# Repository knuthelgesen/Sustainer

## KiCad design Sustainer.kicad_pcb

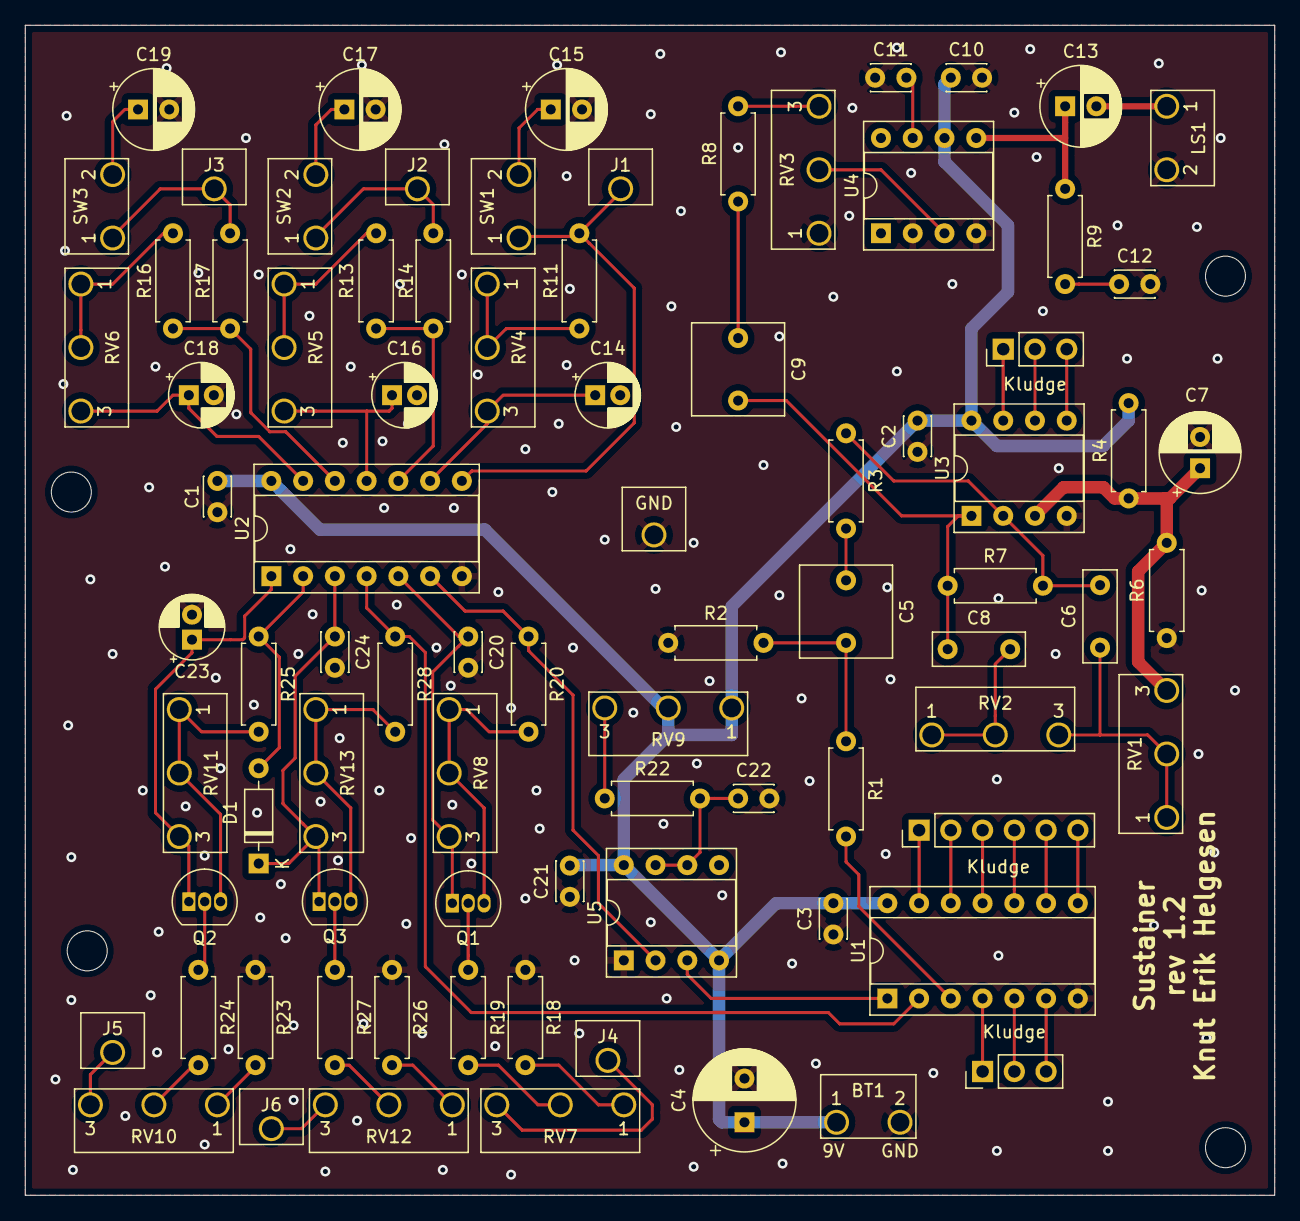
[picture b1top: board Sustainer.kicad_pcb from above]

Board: 2 copper layers, 99.9 x 93.6 mm, 81 parts (0 on the bottom side), 55 nets.

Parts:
BT1: 9V; Connector_2x1_1.5mm
C1, C2, C3, C10, C11, C20, C21, C22, C24: 0.1u; C_Disc_D3.0mm_W2.0mm_P2.50mm
C4: 470u; CP_Radial_D8.0mm_P3.50mm
C5, C9: 1u; C_Rect_L7.2mm_W7.2mm_P5.00mm_FKS2_FKP2_MKS2_MKP2
C6, C8: 0.001u; C_Rect_L7.2mm_W2.5mm_P5.00mm_FKS2_FKP2_MKS2_MKP2
C7, C13, C15, C17, C19: 220u; CP_Radial_D6.3mm_P2.50mm
C12: 0.047u; C_Disc_D3.0mm_W2.0mm_P2.50mm
C14, C23: 1u; CP_Radial_D5.0mm_P2.00mm
C16: 10u; CP_Radial_D5.0mm_P2.00mm
C18: 22u; CP_Radial_D5.0mm_P2.00mm
D1: 1N914; D_DO-35_SOD27_P7.62mm_Horizontal
GND: Connector_1x1_1.5mm
J1, J2, J3, J4, J5, J6: Conn_01x01; Connector_1x1_1.5mm
LS1: Speaker; Connector_2x1_1.5mm
Q1, Q2, Q3: 2N3904; TO-92_Inline
R1: 15k; R_Axial_DIN0207_L6.3mm_D2.5mm_P7.62mm_Horizontal
R2, R18, R23, R26: 8.2k; R_Axial_DIN0207_L6.3mm_D2.5mm_P7.62mm_Horizontal
R3, R7: 4.7M; R_Axial_DIN0207_L6.3mm_D2.5mm_P7.62mm_Horizontal
R4, R6, R19, R24, R27: 100k; R_Axial_DIN0207_L6.3mm_D2.5mm_P7.62mm_Horizontal
R8: 330k; R_Axial_DIN0207_L6.3mm_D2.5mm_P7.62mm_Horizontal
R9: 10; R_Axial_DIN0207_L6.3mm_D2.5mm_P7.62mm_Horizontal
R11, R13, R16, R20, R25, R28: 10k; R_Axial_DIN0207_L6.3mm_D2.5mm_P7.62mm_Horizontal
R14: 470; R_Axial_DIN0207_L6.3mm_D2.5mm_P7.62mm_Horizontal
R17: 1k; R_Axial_DIN0207_L6.3mm_D2.5mm_P7.62mm_Horizontal
R22: 22k; R_Axial_DIN0207_L6.3mm_D2.5mm_P7.62mm_Horizontal
RV1, RV2, RV4, RV5, RV6, RV7, RV8, RV10, RV11, RV12, RV13: 100k; Connector_3x1_1.5mm
RV3: 10k; Connector_3x1_1.5mm
RV9: 500k; Connector_3x1_1.5mm
SW1, SW2, SW3: SW_SPST; Connector_2x1_1.5mm
U1: 4070; DIP-14_W7.62mm_Socket
U2: 40106; DIP-14_W7.62mm_Socket
U3: LM358; DIP-8_W7.62mm_Socket
U4: LM386; DIP-8_W7.62mm_Socket
U5: NE555; DIP-8_W7.62mm_Socket

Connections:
+9V: BT1.1, C1.1, C2.1, C3.1, C4.1, C10.1, C21.1, R4.2, RV9.1, RV9.2, U1.14, U2.14, U3.8, U4.6, U5.4, U5.8
/Filter/input: R1.2, U1.3
/Oscillator1/output: U1.1, U5.3
/Oscillator2/output: R28.1, U1.2, U2.4
/Output/input: C9.1, R8.2
GND: BT1.2, C1.2, C2.2, C3.2, C4.2, C7.2, C10.2, C11.1, C12.2, C14.2, C15.2, C16.2, C17.2, C18.2, C19.2, C20.2, C21.2, C22.2, C23.2, C24.2, GND.1, LS1.2, R2.1, R6.1, R18.2, R23.2, R26.2, RV3.1, U1.7, U2.7, U3.4, U4.2, U4.4, U5.1
unnamed: C5.1, R3.2
unnamed: C5.2, R1.1, R2.2
unnamed: C6.1, RV1.1, RV1.2, RV2.3
unnamed: C6.2, R3.1, R7.2, U3.2
unnamed: C7.1, R4.1, R6.2, RV1.3, U3.3
unnamed: C8.1, C9.2, R7.1, U3.1
unnamed: C8.2, RV2.1, RV2.2
unnamed: C11.2, U4.7
unnamed: C12.1, R9.2
unnamed: C13.1, R9.1, U4.5
unnamed: C13.2, LS1.1
unnamed: C14.1, RV4.3, U2.9
unnamed: C15.1, SW1.2
unnamed: C16.1, RV5.3, U2.11
unnamed: C17.1, SW2.2
unnamed: C18.1, RV6.3, U2.13
unnamed: C19.1, SW3.2
unnamed: C20.1, Q1.1, RV8.3, U2.5
unnamed: C22.1, R22.2, U5.6, U5.7
unnamed: C23.1, Q2.1, RV11.3, U2.1
unnamed: C24.1, D1.1, Q3.1, RV13.3, U2.3
unnamed: D1.2, R25.1, U2.2
unnamed: J1.1, R11.1, SW1.1, U2.8
unnamed: J2.1, R14.1, SW2.1
unnamed: J3.1, R17.1, SW3.1
unnamed: J4.1, RV7.3
unnamed: J5.1, RV10.3
unnamed: J6.1, RV12.3
unnamed: Q1.2, R19.1
unnamed: Q1.3, R20.2, RV8.1, RV8.2
unnamed: Q2.2, R24.1
unnamed: Q2.3, R25.2, RV11.1, RV11.2
unnamed: Q3.2, R27.1
unnamed: Q3.3, R28.2, RV13.1, RV13.2
unnamed: R8.1, RV3.3
unnamed: R11.2, RV4.1, RV4.2
unnamed: R13.1, R14.2, U2.10
unnamed: R13.2, RV5.1, RV5.2
unnamed: R16.1, R17.2, U2.12
unnamed: R16.2, RV6.1, RV6.2
unnamed: R18.1, RV7.1
unnamed: R19.2, RV7.2
unnamed: R20.1, U2.6, U5.2
unnamed: R22.1, RV9.3
unnamed: R23.1, RV10.1
unnamed: R24.2, RV10.2
unnamed: R26.1, RV12.1
unnamed: R27.2, RV12.2
unnamed: RV3.2, U4.3

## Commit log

2019-12-21 More docs, images and css
2020-01-06 Updated docs
2020-01-06 More docs
2020-01-06 Add transistors to the table of components
2020-02-17 Small changes to the Schematics for readability More docs Add abstract for Booster
2020-02-28 Some suggestions for breadboard layout
2020-03-05 More docs and suggested breadboard layouts
